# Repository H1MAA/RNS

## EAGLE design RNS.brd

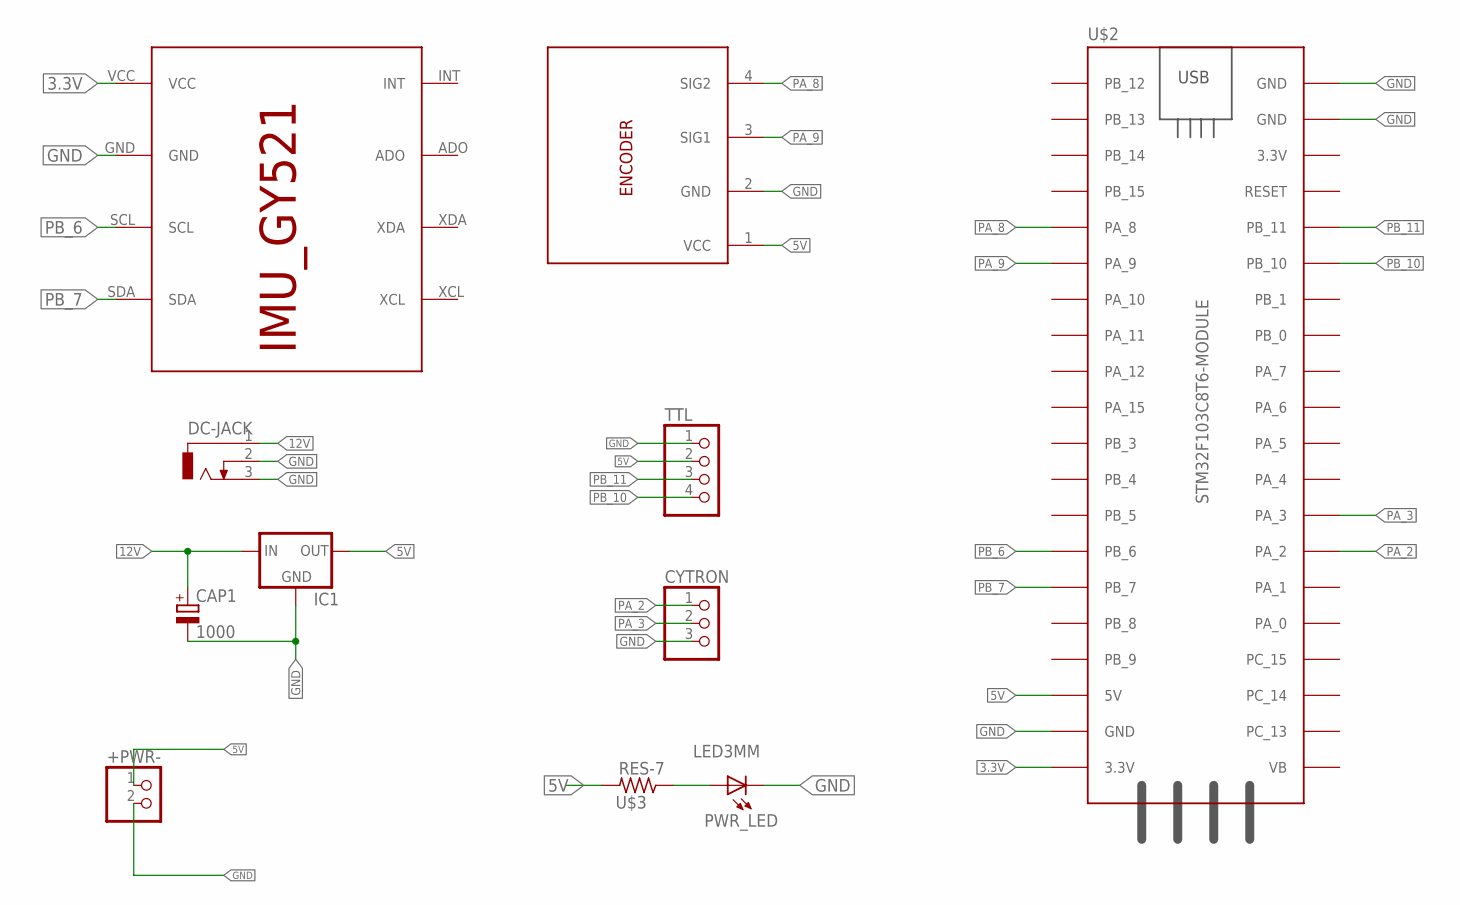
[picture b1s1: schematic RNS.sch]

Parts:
+PWR-: PINHD-1X2; 1X02
CAP1: 1000; E3,5-8
CYTRON: PINHD-1X3; 1X03
DC-JACK: CON_JACK; DCJ0303
IC1: 78XXL
PWR_LED: LED3MM
TTL: PINHD-1X4; 1X04
U$1: ENCODER; 1X04_DATA
U$2: STM32F103C8T6-MODULE
U$3: RES-7; 0204/7
U$4: IMU_ROBOCON_GY521; IMU_GY521

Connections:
3.3V: U$2.3.3V_1 (3.3V), U$4.VCC
5V: +PWR-.1, IC1.OUT, TTL.2, U$1.1 (VCC), U$2.5V, U$3.2
12V: CAP1.+, DC-JACK.1, IC1.IN
A: PWR_LED.A, U$3.1
GND: +PWR-.2, CAP1.-, CYTRON.3, DC-JACK.2, DC-JACK.3, IC1.GND, PWR_LED.K (C), TTL.1, U$1.2 (GND), U$2.GND_1 (GND), U$2.GND_2 (GND), U$2.GND_3 (GND), U$4.GND
PA_2: CYTRON.1, U$2.PA_2
PA_3: CYTRON.2, U$2.PA_3
PA_8: U$1.4 (SIG2), U$2.PA_8
PA_9: U$1.3 (SIG1), U$2.PA_9
PB_6: U$2.PB_6, U$4.SCL
PB_7: U$2.PB_7, U$4.SDA
PB_10: TTL.4, U$2.PB_10
PB_11: TTL.3, U$2.PB_11

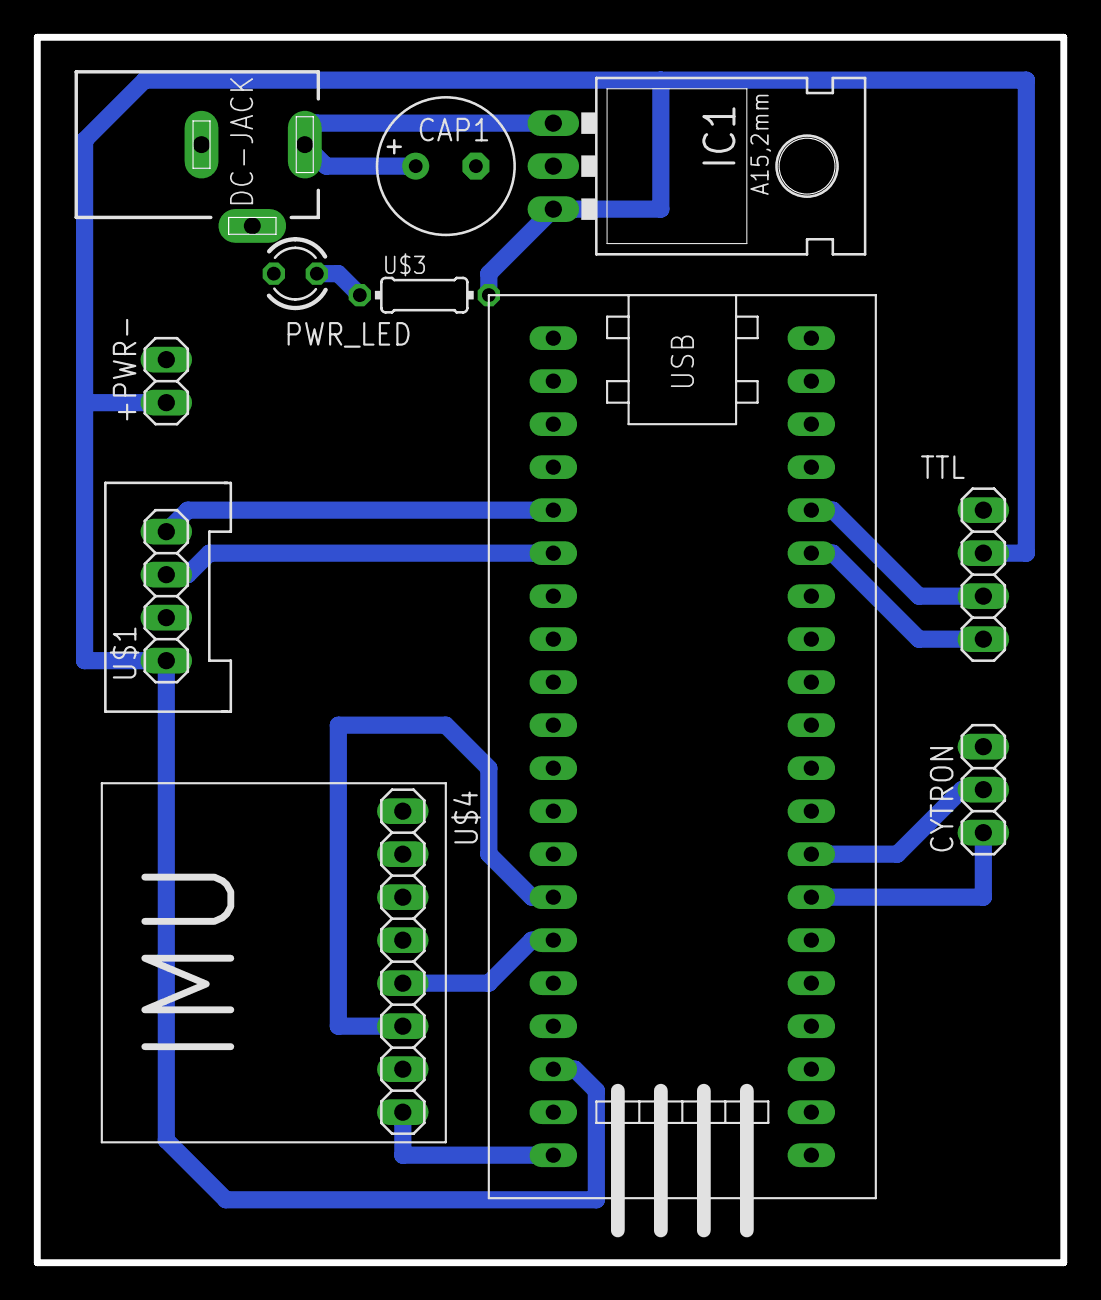
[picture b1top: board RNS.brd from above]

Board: 2 copper layers, 60.6 x 72.4 mm, 11 parts (0 on the bottom side), 13 nets.
